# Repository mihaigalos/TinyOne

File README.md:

# What it is

Breakout board for AtTiny10. Power and RGB leds included, batteries not. :)

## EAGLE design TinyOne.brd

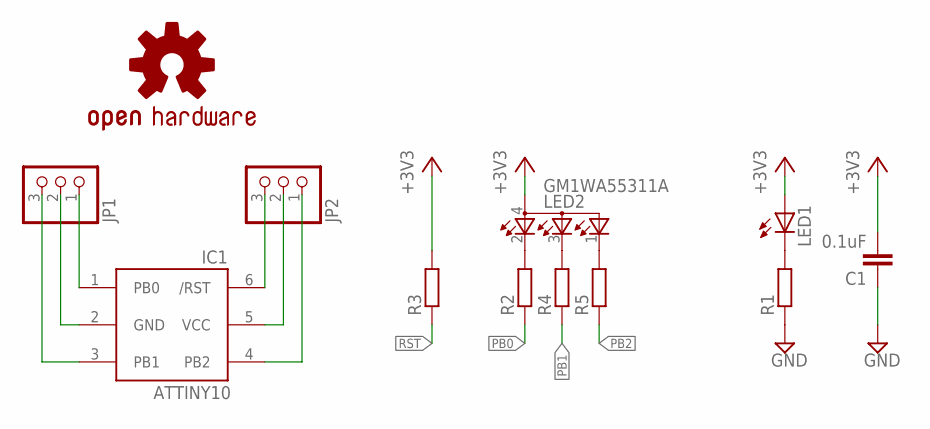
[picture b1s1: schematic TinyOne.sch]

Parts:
C1: 0.1uF; C0603
IC1: ATTINY10; SOT23-6
JP1, JP2: PINHD-1X3CB; 1X03-CLEANBIG
LED1: LEDCHIP-LED0603; CHIP-LED0603
LED2: GM1WA55311A
R1, R2, R3, R4, R5: R-EU_R0603; R0603
U$1: OSHW-LOGOS; OSHW-LOGO-S

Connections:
+3V3: C1.2, IC1.5 (VCC), JP2.2, LED1.A, LED2.4 (A), R3.2
GND: C1.1, IC1.2 (GND), JP1.2, R1.1
unnamed: LED2.2 (CRED), R2.2
unnamed: LED2.3 (CBLUE), R4.2
unnamed: LED2.1 (CGREEN), R5.2
unnamed: LED1.C, R1.2
PB0: IC1.1 (PB0), JP1.1, R2.1
PB1: IC1.3 (PB1), JP1.3, R4.1
PB2: IC1.4 (PB2), JP2.1, R5.1
RST: IC1.6 (/RST), JP2.3, R3.1

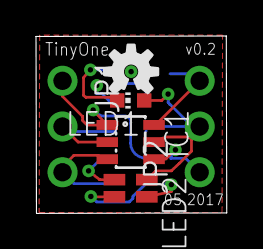
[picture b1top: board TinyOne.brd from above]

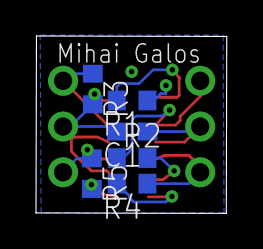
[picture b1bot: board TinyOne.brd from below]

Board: 2 copper layers, 10.6 x 9.9 mm, 12 parts (6 on the bottom side), 10 nets.

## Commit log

2017-05-19 Initial commit of v0.2

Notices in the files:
parts and their libraries:
SparkFun: Licensing: CC v3.0 Share-Alike You are welcome to use this library for commercial purposes.
